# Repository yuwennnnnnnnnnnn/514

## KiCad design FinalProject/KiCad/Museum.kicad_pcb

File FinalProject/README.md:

# Museum Entrance Visitor Counter
### This project designed to count visitors entering and exiting a museum space, using sensors at the entrance and a physical display to present real-time occupancy information.
### Problem being solved：
Museums and galleries often rely on staff to manually count visitors at the entrance. Manual counting is inefficient and often inaccurate during peak hours.
This project automates visitor counting and shows occupancy through a physical gauge display.
### Proposed solution:

Sensing device: A device installed at the museum entrance that uses distance sensors to detect people entering and exiting. The device processes directional movement and wirelessly sends visitor count data.

Display device: physically displays the current visitor count or occupancy level, allowing staff to quickly understand space usage at a glance and adjust lighting and air conditioning accordingly.

### Device Components Table

| Device         | Component    | Part Number            | Function                  |
| -------------- | ------------ | ---------------------- | ------------------------- |
| Sensor Device  | IR Sensor x2 | Sharp GP2Y0A02YK0F     | Detects people enter/exit |
| Sensor Device  | MCU          | Xiao ESP32-c3          | Main controller           |
| Display Device | OLED Display | 0.96″ SSD1306          | Shows visitor count       |
| Display Device | LEDs ×4      | Kingbright WP7113      | Occupancy indicators      |
| Display Device | Button       | APEM 9008T10           | User control light        |
| Display Device | Battery      | Adafruit LiPo 1200 mAh | Power source              |

### Functional video link: https://drive.google.com/file/d/1od8rS6hWe6a75a3NW0yvldowDUYzMvKP/view?usp=drive_link

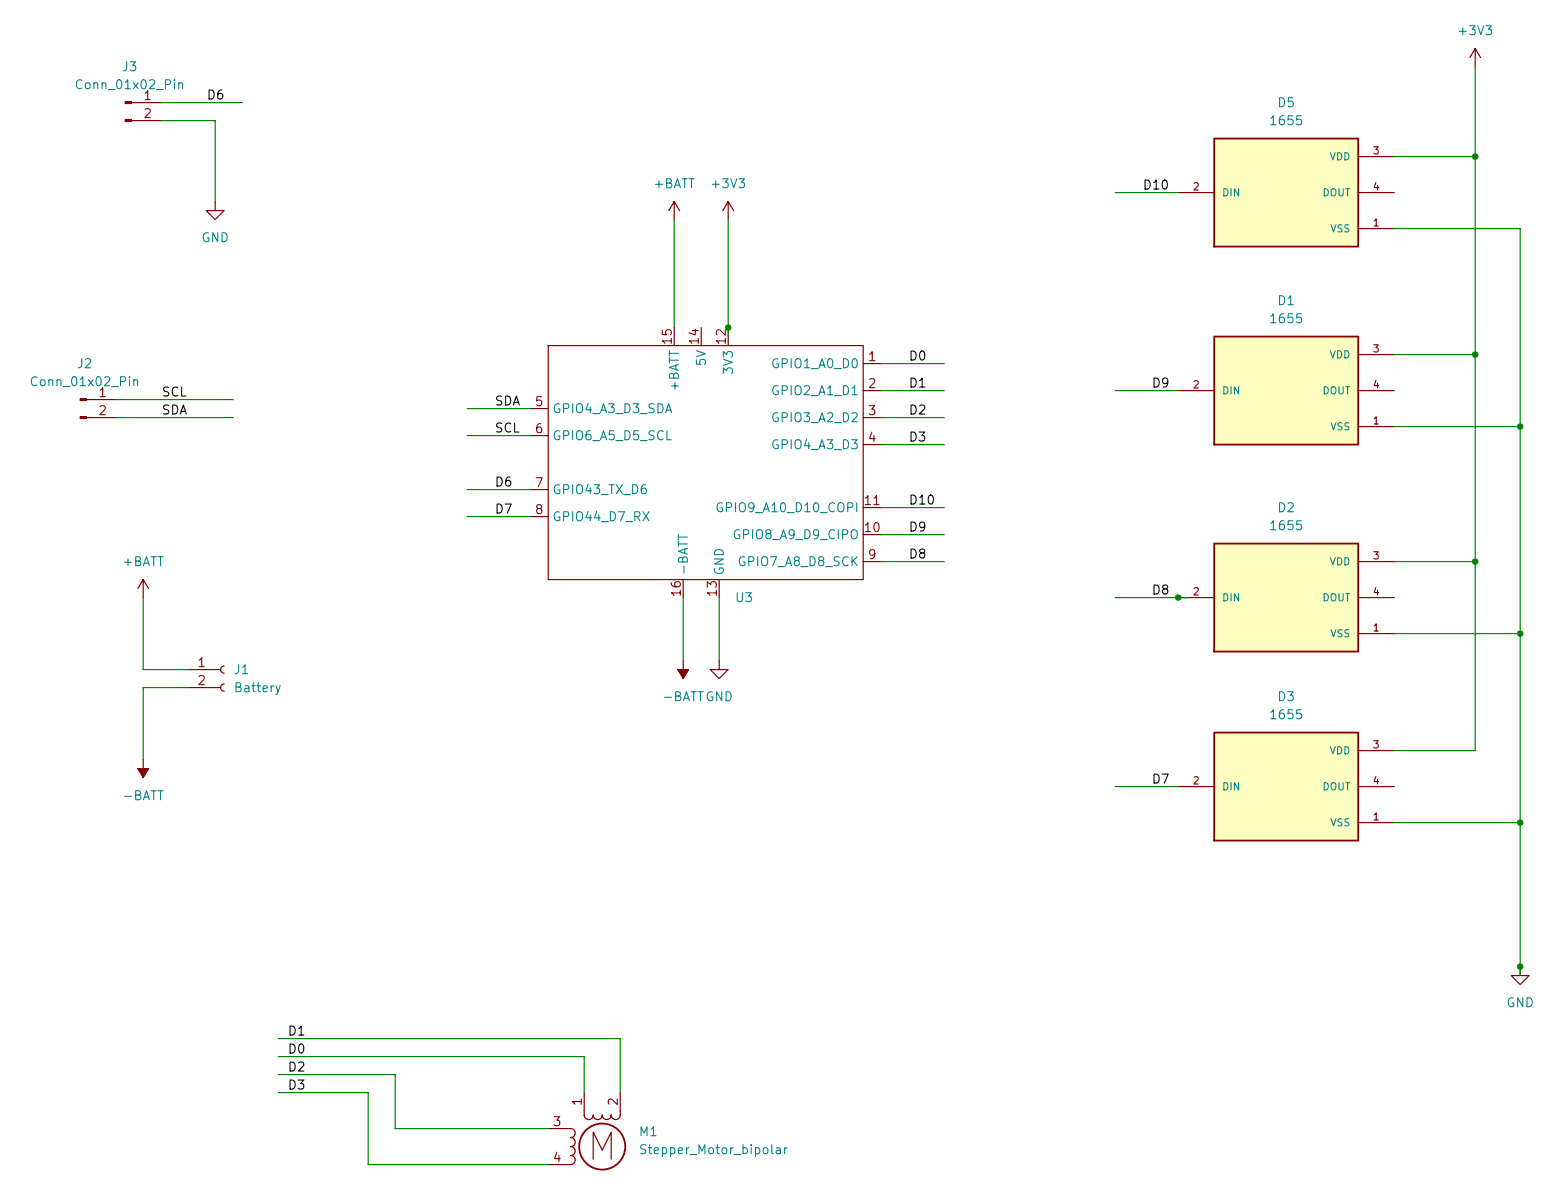
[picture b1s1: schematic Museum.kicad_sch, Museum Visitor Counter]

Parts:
D1, D2, D3, D5: 1655; LED_1655; PARTREV 01
J1: Battery; PinSocket_1x02_P1.00mm_Vertical
J2, J3: Conn_01x02_Pin; PinHeader_1x02_P1.00mm_Vertical
M1: Stepper_Motor_bipolar; x27_stepper
U3: XIAO_ESP32

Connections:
+3V3: D1.3 (VDD), D2.3 (VDD), D3.3 (VDD), D5.3 (VDD), U3.12 (3V3)
+BATT: J1.1, U3.15 (+BATT)
-BATT: J1.2, U3.16 (-BATT)
/D0: M1.1, U3.1 (GPIO1_A0_D0)
/D1: M1.2 (-), U3.2 (GPIO2_A1_D1)
/D2: M1.3, U3.3 (GPIO3_A2_D2)
/D3: M1.4, U3.4 (GPIO4_A3_D3)
/D6: J3.1, U3.7 (GPIO43_TX_D6)
/D7: D3.2 (DIN), U3.8 (GPIO44_D7_RX)
/D8: D2.2 (DIN), U3.9 (GPIO7_A8_D8_SCK)
/D9: D1.2 (DIN), U3.10 (GPIO8_A9_D9_CIPO)
/D10: D5.2 (DIN), U3.11 (GPIO9_A10_D10_COPI)
/SCL: J2.1, U3.6 (GPIO6_A5_D5_SCL)
/SDA: J2.2, U3.5 (GPIO4_A3_D3_SDA)
GND: D1.1 (VSS), D2.1 (VSS), D3.1 (VSS), D5.1 (VSS), J3.2, U3.13 (GND)

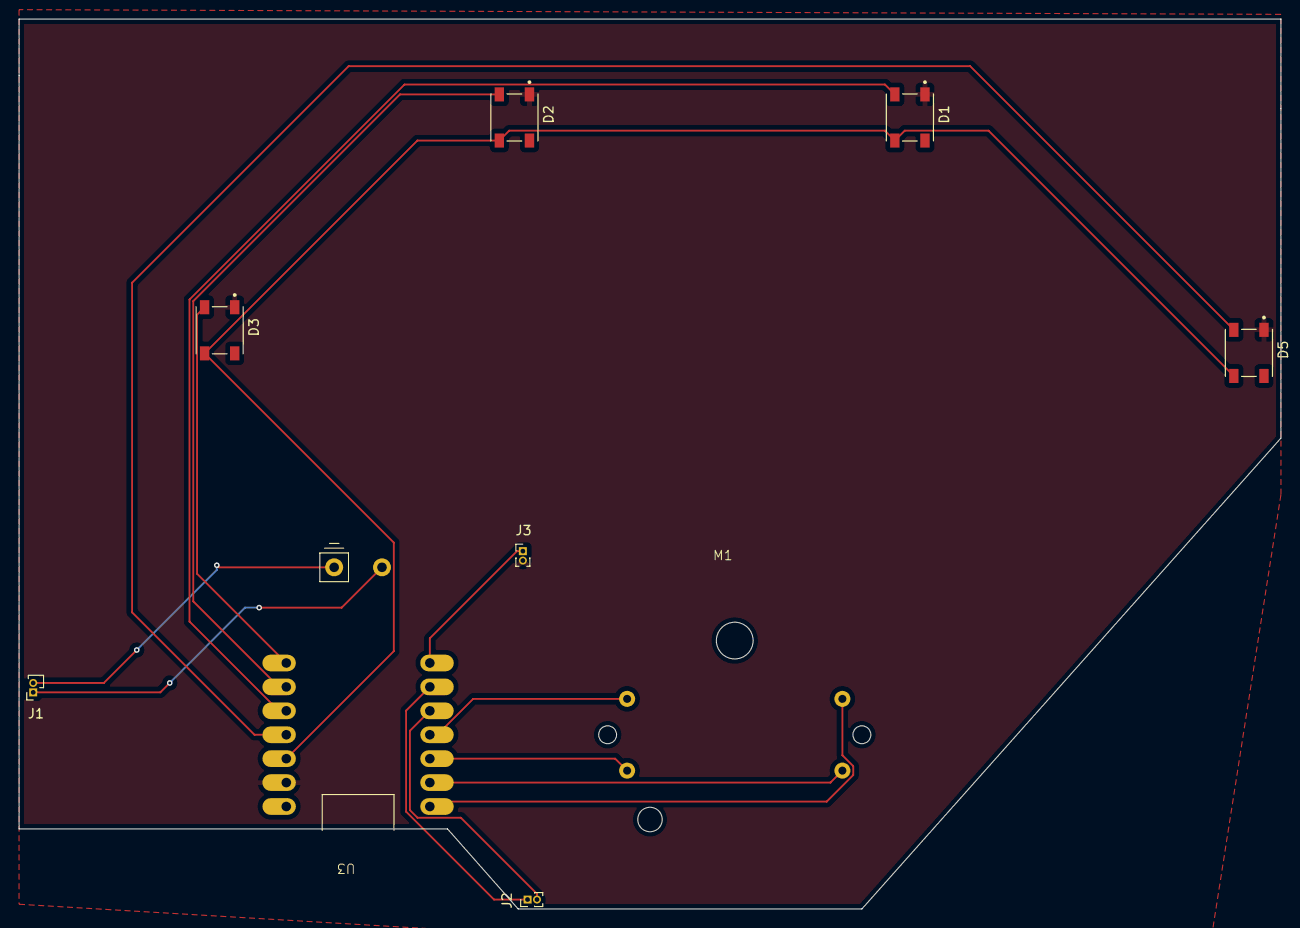
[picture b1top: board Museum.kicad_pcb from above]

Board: 2 copper layers, 134.0 x 94.5 mm, 9 parts (0 on the bottom side), 15 nets.

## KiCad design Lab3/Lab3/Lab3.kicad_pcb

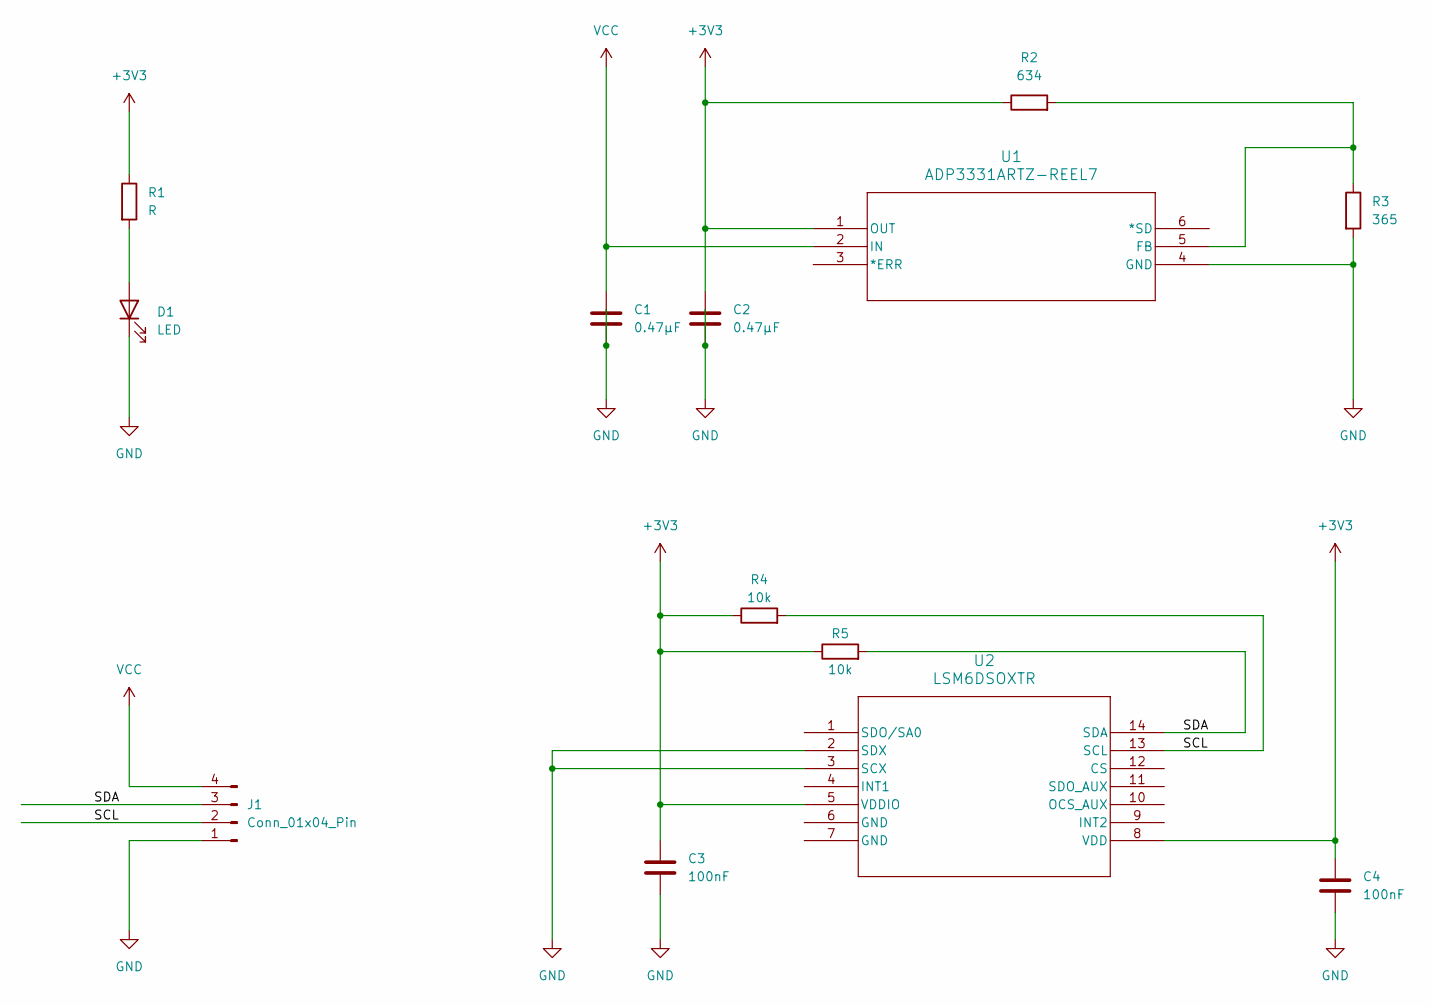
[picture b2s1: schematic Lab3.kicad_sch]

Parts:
C1, C2: 0.47µF; C_0603_1608Metric_Pad1.08x0.95mm_HandSolder
C3, C4: 100nF; C_0603_1608Metric_Pad1.08x0.95mm_HandSolder
D1: LED; LED_0603_1608Metric_Pad1.05x0.95mm_HandSolder
J1: Conn_01x04_Pin; PinHeader_1x04_P1.00mm_Vertical
R1: R; R_0603_1608Metric_Pad0.98x0.95mm_HandSolder
R2: 634; R_0603_1608Metric_Pad0.98x0.95mm_HandSolder
R3: 365; R_0603_1608Metric_Pad0.98x0.95mm_HandSolder
R4, R5: 10k; R_0603_1608Metric_Pad0.98x0.95mm_HandSolder
U1: ADP3331ARTZ-REEL7; RJ_6_ADI
U2: LSM6DSOXTR; LGA-14L_STM

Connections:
+3V3: C2.1, C3.1, C4.1, R1.1, R2.1, R4.1, R5.1, U1.1 (OUT), U2.5 (VDDIO), U2.8 (VDD)
/SCL: J1.2, R4.2, U2.13 (SCL)
/SDA: J1.3, R5.2, U2.14 (SDA)
GND: C1.2, C2.2, C3.2, C4.2, D1.1 (K), J1.1, R3.2, U1.4 (GND), U2.2 (SDX), U2.3 (SCX)
unnamed: D1.2 (A), R1.2
unnamed: R2.2, R3.1, U1.5 (FB)
VCC: C1.1, J1.4, U1.2 (IN)

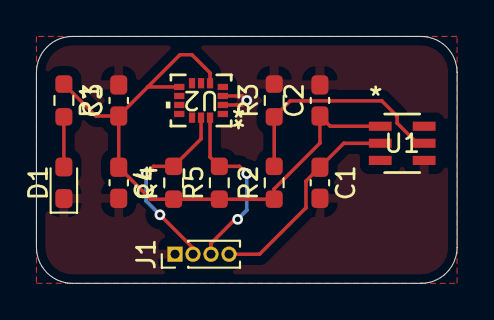
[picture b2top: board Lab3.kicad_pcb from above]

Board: 2 copper layers, 23.4 x 13.7 mm, 13 parts (0 on the bottom side), 7 nets.

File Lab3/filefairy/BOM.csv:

"#","Reference","Qty","Value","Footprint","DNP"
"1","C1, C2","2","0.47µF","Capacitor_SMD:C_0603_1608Metric_Pad1.08x0.95mm_HandSolder",""
"2","C3, C4","2","100nF","Capacitor_SMD:C_0603_1608Metric_Pad1.08x0.95mm_HandSolder",""
"3","D1","1","LED","LED_SMD:LED_0603_1608Metric_Pad1.05x0.95mm_HandSolder",""
"4","J1","1","Conn_01x04_Pin","Connector_PinHeader_1.00mm:PinHeader_1x04_P1.00mm_Vertical",""
"5","R1","1","R","Resistor_SMD:R_0603_1608Metric_Pad0.98x0.95mm_HandSolder",""
"6","R2","1","634","Resistor_SMD:R_0603_1608Metric_Pad0.98x0.95mm_HandSolder",""
"7","R3","1","365","Resistor_SMD:R_0603_1608Metric_Pad0.98x0.95mm_HandSolder",""
"8","R4, R5","2","10k","Resistor_SMD:R_0603_1608Metric_Pad0.98x0.95mm_HandSolder",""
"9","U1","1","ADP3331ARTZ-REEL7","ADP3331:RJ_6_ADI",""
"10","U2","1","LSM6DSOXTR","LSM6D:LGA-14L_STM",""

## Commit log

2026-01-15 Lab2
2026-01-18 Update explanation
2026-01-20 Add datasheets
2026-01-20 Enhance README with project details and images
    Updated the README to include additional details about the project, including images and a device components table.
2026-01-20 Fix formatting of Device Components Table header
2026-01-21 Add additional image to README.md
2026-01-27 add KiCad project files
2026-01-28 Lab4
2026-01-30 add file
2026-02-05 Lab5
2026-03-02 Update sensor code
2026-03-08 Add museum display (BLE client) and updated sensor code (BLE server), PCB design files
2026-03-08 Add functional video link to README
    Added a link to the functional video demonstrating the project.
